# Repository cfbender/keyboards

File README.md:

# The Society of the Crossed Keys

In here you will find my growing list of mechanical keyboard design projects, some of which have been run as local or larger GBs with [KeyHive](https://www.keyhive.xyz).

Please let me know if you have any questions with ordering any PCBs (or let me know if you do it regardless!), or have any questions on how they are designed or function.

Please feel free to open any issues with any cases or PCBs that you have here, and I will do my best to address them!

### Acrylic Case Info

All of my acrylic case files follow the below naming standard:
- All layers are numbered starting with 0, and are numbered up from the bottom
- All layers will be designated with `L<layer number>`
- All feet layers will be designated with `F<layer number>`
- All M3 cases use M3x20mm screws that tap directly into the bottom layer
- All M2 cases will use M3x15+3mm male-to-female brass barrel standoffs where the standoff taps directly into the bottom layer, and M2x6mm screws to screw into the female end of the standoff
- All feet have M4 holes, but I typically have been using M3x14mm screws with M3 nuts on the inside

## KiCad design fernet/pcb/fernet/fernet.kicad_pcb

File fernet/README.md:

# Fernet (_fur-net_)

_"Fernet is an Italian type of amaro, a bitter, aromatic spirit. Fernet is made from a number of herbs and spices which vary according to the brand, but usually include myrrh, rhubarb, chamomile, cardamom, aloe, and especially saffron, with a base of grape distilled spirits."_

A 75% keyboard with a rotary encoder.

This one is really for me since it is only one layout and SMD Elite-C only, but figured I'd put it up here in case anyone is interested in an open source spaced F-row 75% board. More details to follow after initial build.

[Firmware](https://github.com/cfbender/qmk_firmware/tree/fernet/keyboards/fernet)

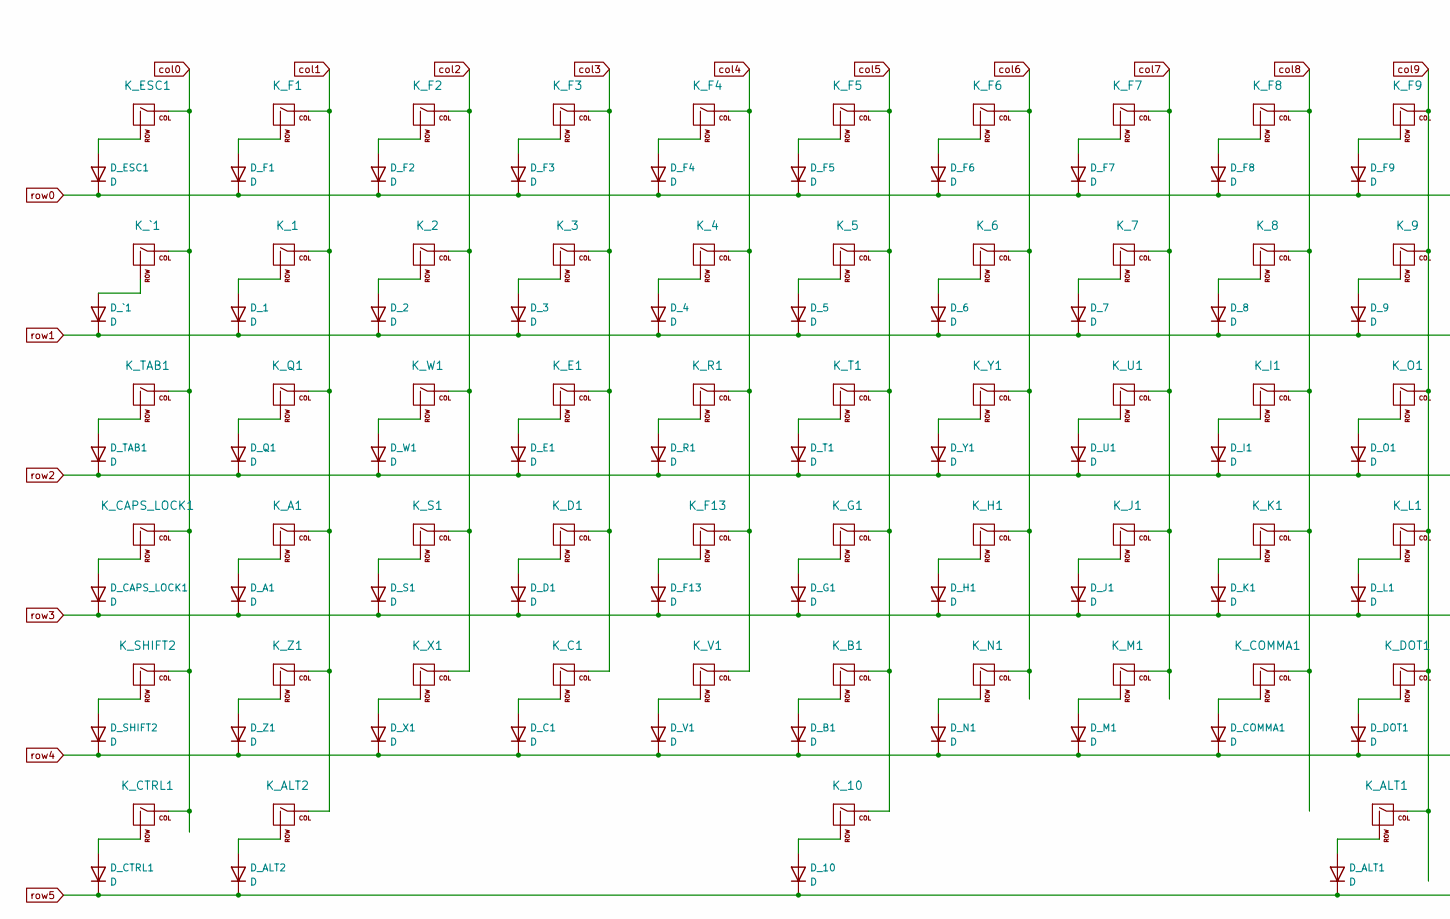
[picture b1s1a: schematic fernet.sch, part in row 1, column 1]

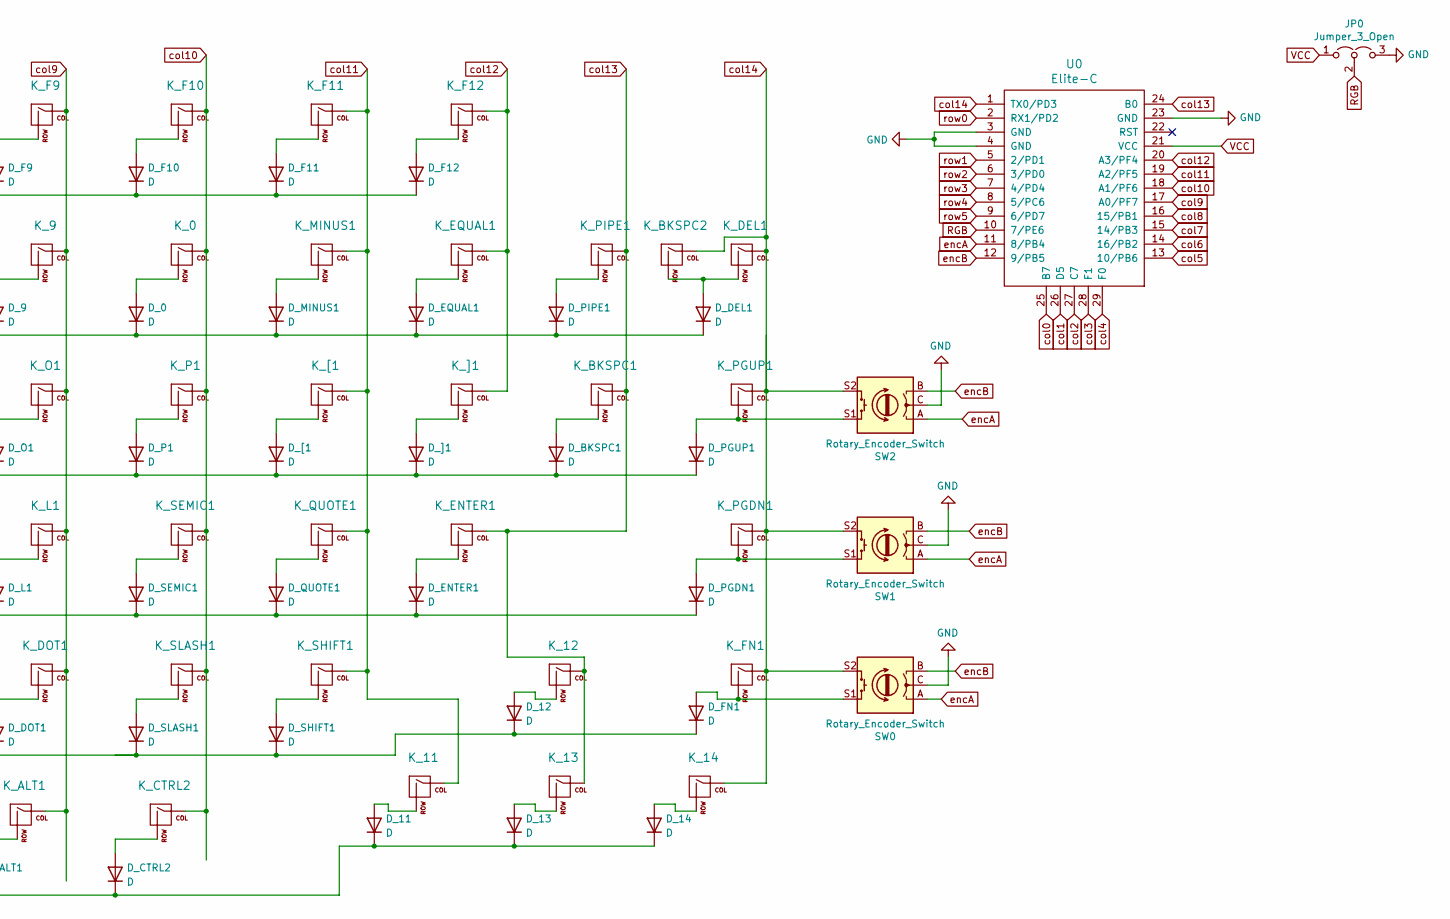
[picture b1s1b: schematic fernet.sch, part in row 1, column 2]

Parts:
D_0, D_1, D_2, D_3, D_4, D_5, D_6, D_7, D_8, D_9, D_10, D_11, D_12, D_13, D_14: D; Diode-Hybrid-Back
D_A1: D; Diode-Hybrid-Back
D_ALT1, D_ALT2: D; Diode-Hybrid-Back
D_B1: D; Diode-Hybrid-Back
D_BKSPC1: D; Diode-Hybrid-Back
D_C1: D; Diode-Hybrid-Back
D_CAPS_LOCK1: D; Diode-Hybrid-Back
D_COMMA1: D; Diode-Hybrid-Back
D_CTRL1, D_CTRL2: D; Diode-Hybrid-Back
D_D1: D; Diode-Hybrid-Back
D_DEL1: D; Diode-Hybrid-Back
D_DOT1: D; Diode-Hybrid-Back
D_E1: D; Diode-Hybrid-Back
D_ENTER1: D; Diode-Hybrid-Back
D_EQUAL1: D; Diode-Hybrid-Back
D_ESC1: D; Diode-Hybrid-Back
D_F1, D_F2, D_F3, D_F4, D_F5, D_F6, D_F7, D_F8, D_F9, D_F10, D_F11, D_F12, D_F13: D; Diode-Hybrid-Back
D_FN1: D; Diode-Hybrid-Back
D_G1: D; Diode-Hybrid-Back
D_H1: D; Diode-Hybrid-Back
D_I1: D; Diode-Hybrid-Back
D_J1: D; Diode-Hybrid-Back
D_K1: D; Diode-Hybrid-Back
D_L1: D; Diode-Hybrid-Back
D_M1: D; Diode-Hybrid-Back
D_MINUS1: D; Diode-Hybrid-Back
D_N1: D; Diode-Hybrid-Back
D_O1: D; Diode-Hybrid-Back
D_P1: D; Diode-Hybrid-Back
D_PGDN1: D; Diode-Hybrid-Back
D_PGUP1: D; Diode-Hybrid-Back
D_PIPE1: D; Diode-Hybrid-Back
D_Q1: D; Diode-Hybrid-Back
D_QUOTE1: D; Diode-Hybrid-Back
D_R1: D; Diode-Hybrid-Back
D_S1: D; Diode-Hybrid-Back
D_SEMIC1: D; Diode-Hybrid-Back
D_SHIFT1, D_SHIFT2: D; Diode-Hybrid-Back
D_SLASH1: D; Diode-Hybrid-Back
D_T1: D; Diode-Hybrid-Back
D_TAB1: D; Diode-Hybrid-Back
D_U1: D; Diode-Hybrid-Back
D_V1: D; Diode-Hybrid-Back
D_W1: D; Diode-Hybrid-Back
D_X1: D; Diode-Hybrid-Back
D_Y1: D; Diode-Hybrid-Back
D_Z1: D; Diode-Hybrid-Back
D_[1: D; Diode-Hybrid-Back
D_]1: D; Diode-Hybrid-Back
D_`1: D; Diode-Hybrid-Back
JP0: Jumper_3_Open; SolderJumperRight
K_0, K_1, K_2, K_3, K_4, K_5, K_6, K_7, K_8, K_9, K_11, K_12, K_13, K_14: KEYSW; MXOnly-1U-NoLED
K_10: KEYSW; MXOnly-7U-ReversedStabilizers-NoLED
K_A1: KEYSW; MXOnly-1U-NoLED
K_ALT1, K_ALT2: KEYSW; MXOnly-1.5U-NoLED
K_B1: KEYSW; MXOnly-1U-NoLED
K_BKSPC1: KEYSW; MXOnly-1.5U-NoLED
K_BKSPC2: KEYSW; MXOnly-2U-NoLED
K_C1: KEYSW; MXOnly-1U-NoLED
K_CAPS_LOCK1: KEYSW; MXOnly-1.75U-NoLED
K_COMMA1: KEYSW; MXOnly-1U-NoLED
K_CTRL1, K_CTRL2: KEYSW; MXOnly-1.5U-NoLED
K_D1: KEYSW; MXOnly-1U-NoLED
K_DEL1: KEYSW; MXOnly-1U-NoLED
K_DOT1: KEYSW; MXOnly-1U-NoLED
K_E1: KEYSW; MXOnly-1U-NoLED
K_ENTER1: KEYSW; MXOnly-2.25U-NoLED
K_EQUAL1: KEYSW; MXOnly-1U-NoLED
K_ESC1: KEYSW; MXOnly-1U-NoLED
K_F1, K_F2, K_F3, K_F4, K_F5, K_F6, K_F7, K_F8, K_F9, K_F10, K_F11, K_F12, K_F13: KEYSW; MXOnly-1U-NoLED
K_FN1: KEYSW; MXOnly-1U-NoLED
K_G1: KEYSW; MXOnly-1U-NoLED
K_H1: KEYSW; MXOnly-1U-NoLED
K_I1: KEYSW; MXOnly-1U-NoLED
K_J1: KEYSW; MXOnly-1U-NoLED
K_K1: KEYSW; MXOnly-1U-NoLED
K_L1: KEYSW; MXOnly-1U-NoLED
K_M1: KEYSW; MXOnly-1U-NoLED
K_MINUS1: KEYSW; MXOnly-1U-NoLED
K_N1: KEYSW; MXOnly-1U-NoLED
K_O1: KEYSW; MXOnly-1U-NoLED
K_P1: KEYSW; MXOnly-1U-NoLED
K_PGDN1: KEYSW; MXOnly-1U-NoLED
K_PGUP1: KEYSW; MXOnly-1U-NoLED
K_PIPE1: KEYSW; MXOnly-1U-NoLED
K_Q1: KEYSW; MXOnly-1U-NoLED
K_QUOTE1: KEYSW; MXOnly-1U-NoLED
K_R1: KEYSW; MXOnly-1U-NoLED
K_S1: KEYSW; MXOnly-1U-NoLED
K_SEMIC1: KEYSW; MXOnly-1U-NoLED
K_SHIFT1: KEYSW; MXOnly-1.75U-NoLED
K_SHIFT2: KEYSW; MXOnly-2.25U-NoLED
K_SLASH1: KEYSW; MXOnly-1U-NoLED
K_T1: KEYSW; MXOnly-1U-NoLED
K_TAB1: KEYSW; MXOnly-1.5U-NoLED
K_U1: KEYSW; MXOnly-1U-NoLED
K_V1: KEYSW; MXOnly-1U-NoLED
K_W1: KEYSW; MXOnly-1U-NoLED
K_X1: KEYSW; MXOnly-1U-NoLED
K_Y1: KEYSW; MXOnly-1U-NoLED
K_Z1: KEYSW; MXOnly-1U-NoLED
K_[1: KEYSW; MXOnly-1U-NoLED
K_]1: KEYSW; MXOnly-1U-NoLED
K_`1: KEYSW; MXOnly-1U-NoLED
SW0, SW1, SW2: Rotary_Encoder_Switch; RotaryEncoder_Alps_EC11E-Switch_Vertical_H20mm
U0: Elite-C; Elite-C-castellated-29pin

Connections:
GND: JP0.3 (B), SW0.C, SW1.C, SW2.C, U0.3 (GND), U0.4 (GND), U0.23 (GND)
unnamed: D_0.2 (A), K_0.2 (ROW)
unnamed: D_1.2 (A), K_1.2 (ROW)
unnamed: D_2.2 (A), K_2.2 (ROW)
unnamed: D_3.2 (A), K_3.2 (ROW)
unnamed: D_4.2 (A), K_4.2 (ROW)
unnamed: D_5.2 (A), K_5.2 (ROW)
unnamed: D_6.2 (A), K_6.2 (ROW)
unnamed: D_7.2 (A), K_7.2 (ROW)
unnamed: D_8.2 (A), K_8.2 (ROW)
unnamed: D_9.2 (A), K_9.2 (ROW)
unnamed: D_10.2 (A), K_10.2 (ROW)
unnamed: D_11.2 (A), K_11.2 (ROW)
unnamed: D_12.2 (A), K_12.2 (ROW)
unnamed: D_13.2 (A), K_13.2 (ROW)
unnamed: D_14.2 (A), K_14.2 (ROW)
unnamed: D_A1.2 (A), K_A1.2 (ROW)
unnamed: D_ALT1.2 (A), K_ALT1.2 (ROW)
unnamed: D_ALT2.2 (A), K_ALT2.2 (ROW)
unnamed: D_B1.2 (A), K_B1.2 (ROW)
unnamed: D_BKSPC1.2 (A), K_BKSPC1.2 (ROW)
unnamed: D_C1.2 (A), K_C1.2 (ROW)
unnamed: D_CAPS_LOCK1.2 (A), K_CAPS_LOCK1.2 (ROW)
unnamed: D_COMMA1.2 (A), K_COMMA1.2 (ROW)
unnamed: D_CTRL1.2 (A), K_CTRL1.2 (ROW)
unnamed: D_CTRL2.2 (A), K_CTRL2.2 (ROW)
unnamed: D_D1.2 (A), K_D1.2 (ROW)
unnamed: D_DEL1.2 (A), K_BKSPC2.2 (ROW), K_DEL1.2 (ROW)
unnamed: D_DOT1.2 (A), K_DOT1.2 (ROW)
unnamed: D_E1.2 (A), K_E1.2 (ROW)
unnamed: D_ENTER1.2 (A), K_ENTER1.2 (ROW)
unnamed: D_EQUAL1.2 (A), K_EQUAL1.2 (ROW)
unnamed: D_ESC1.2 (A), K_ESC1.2 (ROW)
unnamed: D_F1.2 (A), K_F1.2 (ROW)
unnamed: D_F2.2 (A), K_F2.2 (ROW)
unnamed: D_F3.2 (A), K_F3.2 (ROW)
unnamed: D_F4.2 (A), K_F4.2 (ROW)
unnamed: D_F5.2 (A), K_F5.2 (ROW)
unnamed: D_F6.2 (A), K_F6.2 (ROW)
unnamed: D_F7.2 (A), K_F7.2 (ROW)
unnamed: D_F8.2 (A), K_F8.2 (ROW)
unnamed: D_F9.2 (A), K_F9.2 (ROW)
unnamed: D_F10.2 (A), K_F10.2 (ROW)
unnamed: D_F11.2 (A), K_F11.2 (ROW)
unnamed: D_F12.2 (A), K_F12.2 (ROW)
unnamed: D_F13.2 (A), K_F13.2 (ROW)
unnamed: D_FN1.2 (A), K_FN1.2 (ROW), SW0.S1
unnamed: D_G1.2 (A), K_G1.2 (ROW)
unnamed: D_H1.2 (A), K_H1.2 (ROW)
unnamed: D_I1.2 (A), K_I1.2 (ROW)
unnamed: D_J1.2 (A), K_J1.2 (ROW)
unnamed: D_K1.2 (A), K_K1.2 (ROW)
unnamed: D_L1.2 (A), K_L1.2 (ROW)
unnamed: D_M1.2 (A), K_M1.2 (ROW)
unnamed: D_MINUS1.2 (A), K_MINUS1.2 (ROW)
unnamed: D_N1.2 (A), K_N1.2 (ROW)
unnamed: D_O1.2 (A), K_O1.2 (ROW)
unnamed: D_P1.2 (A), K_P1.2 (ROW)
unnamed: D_PGDN1.2 (A), K_PGDN1.2 (ROW), SW1.S1
unnamed: D_PGUP1.2 (A), K_PGUP1.2 (ROW), SW2.S1
unnamed: D_PIPE1.2 (A), K_PIPE1.2 (ROW)
unnamed: D_Q1.2 (A), K_Q1.2 (ROW)
unnamed: D_QUOTE1.2 (A), K_QUOTE1.2 (ROW)
unnamed: D_R1.2 (A), K_R1.2 (ROW)
unnamed: D_S1.2 (A), K_S1.2 (ROW)
unnamed: D_SEMIC1.2 (A), K_SEMIC1.2 (ROW)
unnamed: D_SHIFT1.2 (A), K_SHIFT1.2 (ROW)
unnamed: D_SHIFT2.2 (A), K_SHIFT2.2 (ROW)
unnamed: D_SLASH1.2 (A), K_SLASH1.2 (ROW)
unnamed: D_T1.2 (A), K_T1.2 (ROW)
unnamed: D_TAB1.2 (A), K_TAB1.2 (ROW)
unnamed: D_U1.2 (A), K_U1.2 (ROW)
unnamed: D_V1.2 (A), K_V1.2 (ROW)
unnamed: D_W1.2 (A), K_W1.2 (ROW)
unnamed: D_X1.2 (A), K_X1.2 (ROW)
unnamed: D_Y1.2 (A), K_Y1.2 (ROW)
unnamed: D_Z1.2 (A), K_Z1.2 (ROW)
unnamed: D_[1.2 (A), K_[1.2 (ROW)
unnamed: D_]1.2 (A), K_]1.2 (ROW)
unnamed: D_`1.2 (A), K_`1.2 (ROW)
RGB: JP0.2 (C), U0.10 (7/PE6)
VCC: JP0.1 (A), U0.21 (VCC)
col0: K_CAPS_LOCK1.1 (COL), K_CTRL1.1 (COL), K_ESC1.1 (COL), K_SHIFT2.1 (COL), K_TAB1.1 (COL), K_`1.1 (COL), U0.25 (B7)
col1: K_1.1 (COL), K_A1.1 (COL), K_ALT2.1 (COL), K_F1.1 (COL), K_Q1.1 (COL), K_Z1.1 (COL), U0.26 (D5)
col2: K_2.1 (COL), K_F2.1 (COL), K_S1.1 (COL), K_W1.1 (COL), K_X1.1 (COL), U0.27 (C7)
col3: K_3.1 (COL), K_C1.1 (COL), K_D1.1 (COL), K_E1.1 (COL), K_F3.1 (COL), U0.28 (F1)
col4: K_4.1 (COL), K_F4.1 (COL), K_F13.1 (COL), K_R1.1 (COL), K_V1.1 (COL), U0.29 (F0)
col5: K_5.1 (COL), K_10.1 (COL), K_B1.1 (COL), K_F5.1 (COL), K_G1.1 (COL), K_T1.1 (COL), U0.13 (10/PB6)
col6: K_6.1 (COL), K_F6.1 (COL), K_H1.1 (COL), K_N1.1 (COL), K_Y1.1 (COL), U0.14 (16/PB2)
col7: K_7.1 (COL), K_F7.1 (COL), K_J1.1 (COL), K_M1.1 (COL), K_U1.1 (COL), U0.15 (14/PB3)
col8: K_8.1 (COL), K_COMMA1.1 (COL), K_F8.1 (COL), K_I1.1 (COL), K_K1.1 (COL), U0.16 (15/PB1)
col9: K_9.1 (COL), K_ALT1.1 (COL), K_DOT1.1 (COL), K_F9.1 (COL), K_L1.1 (COL), K_O1.1 (COL), U0.17 (A0/PF7)
col10: K_0.1 (COL), K_CTRL2.1 (COL), K_F10.1 (COL), K_P1.1 (COL), K_SEMIC1.1 (COL), K_SLASH1.1 (COL), U0.18 (A1/PF6)
col11: K_11.1 (COL), K_F11.1 (COL), K_MINUS1.1 (COL), K_QUOTE1.1 (COL), K_SHIFT1.1 (COL), K_[1.1 (COL), U0.19 (A2/PF5)
col12: K_EQUAL1.1 (COL), K_F12.1 (COL), K_]1.1 (COL), U0.20 (A3/PF4)
col13: K_12.1 (COL), K_13.1 (COL), K_BKSPC1.1 (COL), K_ENTER1.1 (COL), K_PIPE1.1 (COL), U0.24 (B0)
col14: K_14.1 (COL), K_BKSPC2.1 (COL), K_DEL1.1 (COL), K_FN1.1 (COL), K_PGDN1.1 (COL), K_PGUP1.1 (COL), SW0.S2, SW1.S2, SW2.S2, U0.1 (TX0/PD3)
encA: SW0.A, SW1.A, SW2.A, U0.11 (8/PB4)
encB: SW0.B, SW1.B, SW2.B, U0.12 (9/PB5)
row0: D_ESC1.1 (K), D_F1.1 (K), D_F2.1 (K), D_F3.1 (K), D_F4.1 (K), D_F5.1 (K), D_F6.1 (K), D_F7.1 (K), D_F8.1 (K), D_F9.1 (K), D_F10.1 (K), D_F11.1 (K), D_F12.1 (K), U0.2 (RX1/PD2)
row1: D_0.1 (K), D_1.1 (K), D_2.1 (K), D_3.1 (K), D_4.1 (K), D_5.1 (K), D_6.1 (K), D_7.1 (K), D_8.1 (K), D_9.1 (K), D_DEL1.1 (K), D_EQUAL1.1 (K), D_MINUS1.1 (K), D_PIPE1.1 (K), D_`1.1 (K), U0.5 (2/PD1)
row2: D_BKSPC1.1 (K), D_E1.1 (K), D_I1.1 (K), D_O1.1 (K), D_P1.1 (K), D_PGUP1.1 (K), D_Q1.1 (K), D_R1.1 (K), D_T1.1 (K), D_TAB1.1 (K), D_U1.1 (K), D_W1.1 (K), D_Y1.1 (K), D_[1.1 (K), D_]1.1 (K), U0.6 (3/PD0)
row3: D_A1.1 (K), D_CAPS_LOCK1.1 (K), D_D1.1 (K), D_ENTER1.1 (K), D_F13.1 (K), D_G1.1 (K), D_H1.1 (K), D_J1.1 (K), D_K1.1 (K), D_L1.1 (K), D_PGDN1.1 (K), D_QUOTE1.1 (K), D_S1.1 (K), D_SEMIC1.1 (K), U0.7 (4/PD4)
row4: D_12.1 (K), D_B1.1 (K), D_C1.1 (K), D_COMMA1.1 (K), D_DOT1.1 (K), D_FN1.1 (K), D_M1.1 (K), D_N1.1 (K), D_SHIFT1.1 (K), D_SHIFT2.1 (K), D_SLASH1.1 (K), D_V1.1 (K), D_X1.1 (K), D_Z1.1 (K), U0.8 (5/PC6)
row5: D_10.1 (K), D_11.1 (K), D_13.1 (K), D_14.1 (K), D_ALT1.1 (K), D_ALT2.1 (K), D_CTRL1.1 (K), D_CTRL2.1 (K), U0.9 (6/PD7)

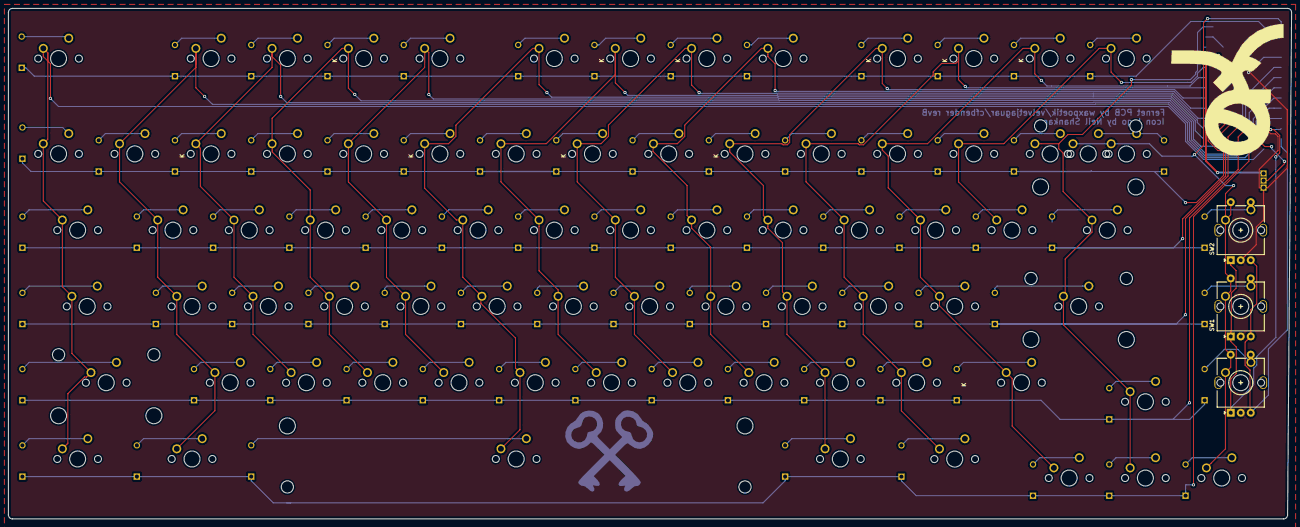
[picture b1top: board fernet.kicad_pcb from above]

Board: 2 copper layers, 320.5 x 127.5 mm, 164 parts (1 on the bottom side), 105 nets.

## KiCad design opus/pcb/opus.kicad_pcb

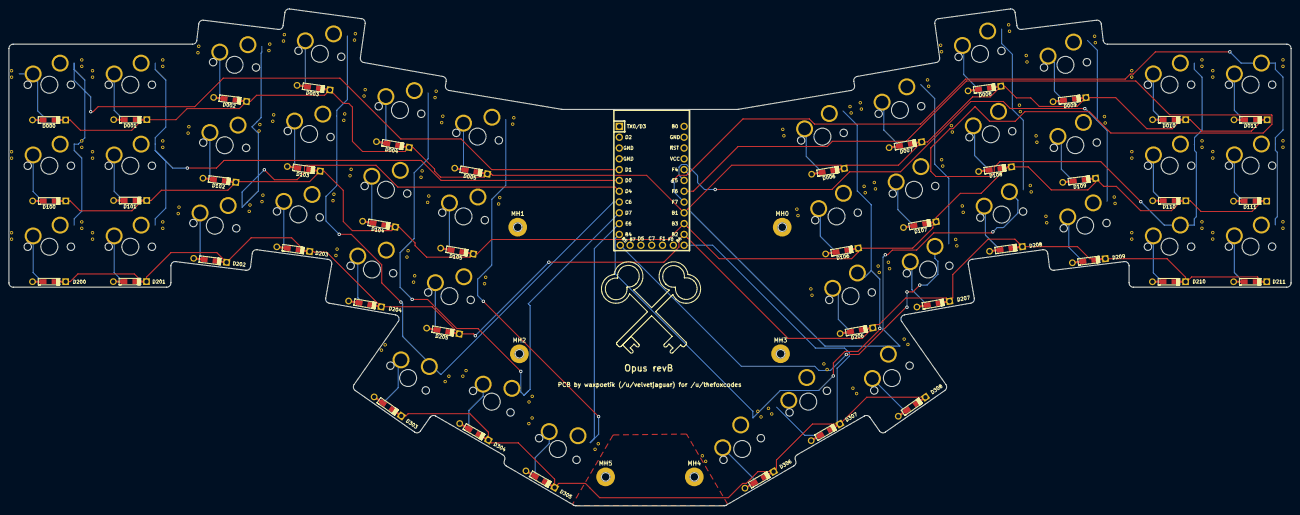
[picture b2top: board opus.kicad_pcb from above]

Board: 2 copper layers, 301.6 x 116.9 mm, 91 parts (0 on the bottom side), 59 nets.

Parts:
D000, D001, D002, D003, D004, D005, D006, D007, D008, D009, D010, D011, D100, D101, D102, D103, D104, D105, D106, D107, D108, D109, D110, D111, D200, D201, D202, D203, D204, D205, D206, D207, D208, D209, D210, D211, D303, D304, D305, D306, D307, D308: 1N4148; Diode-dual
K000, K001, K002, K003, K004, K005, K006, K007, K008, K009, K010, K011, K100, K101, K102, K103, K104, K105, K106, K107, K108, K109, K110, K111, K200, K201, K202, K203, K204, K205, K206, K207, K208, K209, K210, K211, K303, K304, K305, K306, K307, K308: KEYSW; MXOnly-1U-Hotswap-Antishear
MH0, MH1, MH2, MH3, MH4, MH5: MountingHole_Pad; MountingHole_2.2mm_M2_Pad
U0: ProMicro; Elite-C

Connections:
GND: U0.3, U0.4, U0.23
unnamed: D000.2, K000.1
unnamed: D001.2, K001.1
unnamed: D002.2, K002.1
unnamed: D003.2, K003.1
unnamed: D004.2, K004.1
unnamed: D005.2, K005.1
unnamed: D006.2, K006.1
unnamed: D007.2, K007.1
unnamed: D008.2, K008.1
unnamed: D009.2, K009.1
unnamed: D010.2, K010.1
unnamed: D011.2, K011.1
unnamed: D100.2, K100.1
unnamed: D101.2, K101.1
unnamed: D102.2, K102.1
unnamed: D103.2, K103.1
unnamed: D104.2, K104.1
unnamed: D105.2, K105.1
unnamed: D106.2, K106.1
unnamed: D107.2, K107.1
unnamed: D108.2, K108.1
unnamed: D109.2, K109.1
unnamed: D110.2, K110.1
unnamed: D111.2, K111.1
unnamed: D200.2, K200.1
unnamed: D201.2, K201.1
unnamed: D202.2, K202.1
unnamed: D203.2, K203.1
unnamed: D204.2, K204.1
unnamed: D205.2, K205.1
unnamed: D206.2, K206.1
unnamed: D207.2, K207.1
unnamed: D208.2, K208.1
unnamed: D209.2, K209.1
unnamed: D210.2, K210.1
unnamed: D211.2, K211.1
unnamed: D303.2, K303.1
unnamed: D304.2, K304.1
unnamed: D305.2, K305.1
unnamed: D306.2, K306.1
unnamed: D307.2, K307.1
unnamed: D308.2, K308.1
col0: K000.2, K100.2, K200.2, U0.5
col1: K001.2, K101.2, K201.2, U0.6
col2: K002.2, K102.2, K202.2, U0.7
col3: K003.2, K103.2, K203.2, K303.2, U0.8
col4: K004.2, K104.2, K204.2, K304.2, U0.9
col5: K005.2, K105.2, K205.2, K305.2, U0.10
col6: K006.2, K106.2, K206.2, K306.2, U0.11
col7: K007.2, K107.2, K207.2, K307.2, U0.12
col8: K008.2, K108.2, K208.2, K308.2, U0.20
col9: K009.2, K109.2, K209.2, U0.19
col10: K010.2, K110.2, K210.2, U0.18
col11: K011.2, K111.2, K211.2, U0.17
row0: D000.1, D001.1, D002.1, D003.1, D004.1, D005.1, D006.1, D007.1, D008.1, D009.1, D010.1, D011.1, U0.16
row1: D100.1, D101.1, D102.1, D103.1, D104.1, D105.1, D106.1, D107.1, D108.1, D109.1, D110.1, D111.1, U0.15
row2: D200.1, D201.1, D202.1, D203.1, D204.1, D205.1, D206.1, D207.1, D208.1, D209.1, D210.1, D211.1, U0.14
row3: D303.1, D304.1, D305.1, D306.1, D307.1, D308.1, U0.13

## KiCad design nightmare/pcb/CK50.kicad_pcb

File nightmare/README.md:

# Crossed Keys Nightmare

A 50% pseudo-TMO50 clone with an adjusted bottom row, designed on the cheap with a Pro Micro and 3D Printed case.

Keyboard/Case Designer: [cfbender](https://github.com/codybender) with help from Reggatronics/Reggalicious

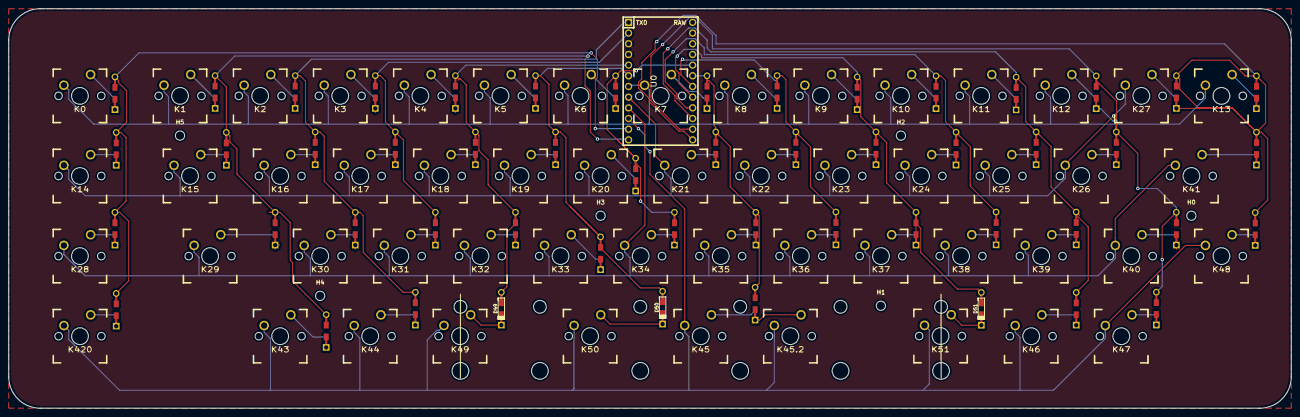
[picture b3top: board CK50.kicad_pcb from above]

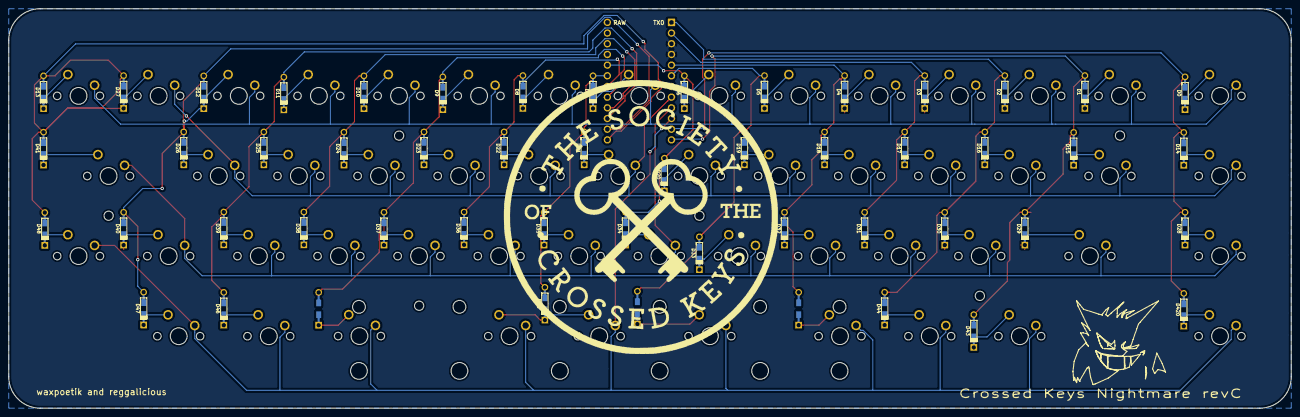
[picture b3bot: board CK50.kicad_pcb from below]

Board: 2 copper layers, 305.0 x 95.0 mm, 112 parts (49 on the bottom side), 70 nets.

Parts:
D0, D1, D2, D3, D4, D5, D6, D7, D8, D9, D10, D11, D12, D13, D14, D15, D16, D17, D18, D19, D20, D21, D22, D23, D24, D25, D26, D27, D28, D29, D30, D31, D32, D33, D34, D35, D36, D37, D38, D39, D40, D41, D43, D44, D45, D46, D47, D48, D49, D50, D51, D420: 1N4148; Diode-dual
H0, H1, H2, H3, H4, H5: MountingHole_2.2mm_M2
K0, K1, K2, K3, K4, K5, K6, K7, K8, K9, K10, K11, K12, K13, K14, K16, K17, K18, K19, K20, K21, K22, K23, K24, K25, K26, K27, K28, K30, K31, K32, K33, K34, K35, K36, K37, K38, K39, K43, K47, K48, K49, K51, K420: KEYSW; MX_PCB_100H
K15, K40, K44, K46: KEYSW; MX_PCB_125H
K29, K41: KEYSW; MX_PCB_175H
K45: KEYSW; MX_PCB_700H
K45.2: KEYSW; MX_PCB_275H
K50: KEYSW; MX_PCB_225H
U0: ProMicro; ARDUINO_PRO_MICRO

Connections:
/col0: D0.2, D14.2, D28.2, D420.2, U0.11
/col1: D1.2, D15.2, D29.2, D43.2, U0.12
/col2: D2.2, D16.2, D30.2, D44.2, U0.1
/col3: D3.2, D17.2, D31.2, U0.2
/col4: D4.2, D18.2, D32.2, D49.2, U0.5
/col5: D5.2, D19.2, D33.2, D50.2, U0.6
/col6: D6.2, D20.2, D34.2, U0.20
/col7: D7.2, D21.2, D35.2, D45.2, U0.19
/col8: D8.2, D22.2, D36.2, U0.18
/col9: D9.2, D23.2, D37.2, D51.2, U0.17
/col10: D10.1, D10.2, D24.2, D38.2, K10.1, U0.16
/col11: D11.2, D25.2, D39.2, D46.2, U0.15
/col12: D12.2, D26.2, D40.2, D47.2, U0.14
/col13: D13.2, D27.2, D41.2, D48.2, U0.13
/row0: K0.2, K1.2, K2.2, K3.2, K4.2, K5.2, K6.2, K7.2, K8.2, K9.2, K10.2, K11.2, K12.2, K13.2, U0.7
/row1: K14.2, K15.2, K16.2, K17.2, K18.2, K19.2, K20.2, K21.2, K22.2, K23.2, K24.2, K25.2, K26.2, K27.2, U0.8
/row2: K28.2, K29.2, K30.2, K31.2, K32.2, K33.2, K34.2, K35.2, K36.2, K37.2, K38.2, K39.2, K40.2, K41.2, U0.9
/row3: K43.2, K44.2, K45.2, K45.2.2, K46.2, K47.2, K48.2, K49.2, K50.2, K51.2, K420.2, U0.10
GND: U0.3, U0.4, U0.23
unnamed: D0.1, K0.1
unnamed: D1.1, K1.1
unnamed: D2.1, K2.1
unnamed: D3.1, K3.1
unnamed: D4.1, K4.1
unnamed: D5.1, K5.1
unnamed: D6.1, K6.1
unnamed: D7.1, K7.1
unnamed: D8.1, K8.1
unnamed: D9.1, K9.1
unnamed: D11.1, K11.1
unnamed: D12.1, K12.1
unnamed: D13.1, K13.1
unnamed: D14.1, K14.1
unnamed: D15.1, K15.1
unnamed: D16.1, K16.1
unnamed: D17.1, K17.1
unnamed: D18.1, K18.1
unnamed: D19.1, K19.1
unnamed: D20.1, K20.1
unnamed: D21.1, K21.1
unnamed: D22.1, K22.1
unnamed: D23.1, K23.1
unnamed: D24.1, K24.1
unnamed: D25.1, K25.1
unnamed: D26.1, K26.1
unnamed: D27.1, K27.1
unnamed: D28.1, K28.1
unnamed: D29.1, K29.1
unnamed: D30.1, K30.1
unnamed: D31.1, K31.1
unnamed: D32.1, K32.1
unnamed: D33.1, K33.1
unnamed: D34.1, K34.1
unnamed: D35.1, K35.1
unnamed: D36.1, K36.1
unnamed: D37.1, K37.1
unnamed: D38.1, K38.1
unnamed: D39.1, K39.1
unnamed: D40.1, K40.1
unnamed: D41.1, K41.1
unnamed: D43.1, K43.1
unnamed: D44.1, K44.1
unnamed: D45.1, K45.1, K45.2.1
unnamed: D46.1, K46.1
unnamed: D47.1, K47.1
unnamed: D48.1, K48.1
unnamed: D49.1, K49.1
unnamed: D50.1, K50.1
unnamed: D51.1, K51.1
unnamed: D420.1, K420.1

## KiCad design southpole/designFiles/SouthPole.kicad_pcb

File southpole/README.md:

# Crossed Keys Southpole

A southpaw numpad with a classic 7u 65% design base.

Keyboard/Case Designer: [Cody Bender](https://github.com/codybender)  

Assembly guide: [On Google Drive](https://drive.google.com/open?id=1JN_OK8rfhoJso8HBKvpQtmv_5men5zyt0q0xczGZrWI)

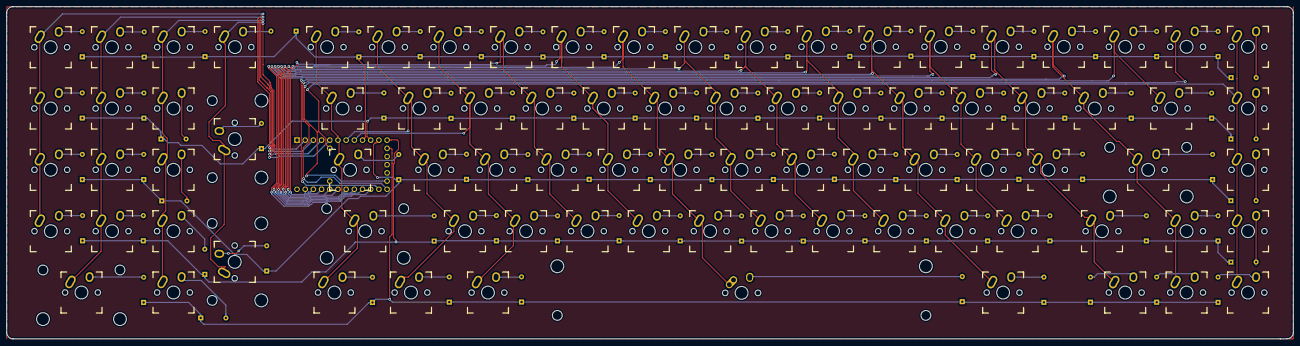
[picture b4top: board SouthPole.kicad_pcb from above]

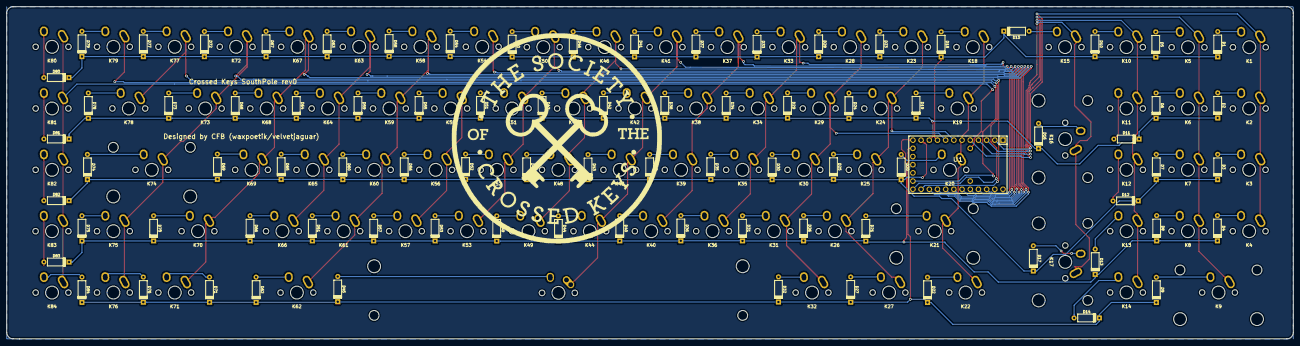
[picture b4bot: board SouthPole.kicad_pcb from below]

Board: 2 copper layers, 399.0 x 103.0 mm, 169 parts (85 on the bottom side), 110 nets.

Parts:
D1, D2, D3, D4, D5, D6, D7, D8, D9, D10, D11, D12, D13, D14, D15, D16, D17, D18, D19, D20, D21, D22, D23, D24, D25, D26, D27, D28, D29, D30, D31, D32, D33, D34, D35, D36, D37, D38, D39, D40, D41, D42, D43, D44, D45, D46, D47, D48, D49, D50, D51, D52, D53, D54, D55, D56, D57, D58, D59, D60, D61, D62, D63, D64, D65, D66, D67, D68, D69, D70, D71, D72, D73, D74, D75, D76, D77, D78, D79, D80, D81, D82, D83, D84: D; D_axial
K1, K2, K3, K4, K5, K6, K7, K8, K10, K11, K12, K13, K14, K15, K18, K23, K24, K25, K26, K28, K29, K30, K31, K33, K34, K35, K36, K37, K38, K39, K40, K41, K42, K43, K44, K46, K47, K48, K49, K50, K51, K52, K53, K54, K55, K56, K57, K58, K59, K60, K61, K63, K64, K65, K66, K67, K68, K69, K71, K72, K73, K75, K76, K77, K79, K80, K81, K82, K83, K84: KEYSW; Mx_Alps_100
K9, K16, K17: KEYSW; Mx_Alps_200
K19, K62, K78: KEYSW; Mx_Alps_150
K20, K70: KEYSW; Mx_Alps_175
K21, K74: KEYSW; Mx_Alps_225
K22, K27, K32: KEYSW; Mx_Alps_125
K45: KEYSW; MX-7U-ReversedStabilizers-NoLED
U1: TEENSY2.0; Teensy_20

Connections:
/col0: K1.1, K2.1, K3.1, K4.1, U1.2
/col1: K5.1, K6.1, K7.1, K8.1, K9.1, U1.3
/col2: K10.1, K11.1, K12.1, K13.1, K14.1, U1.4
/col3: K15.1, K16.1, K17.1, U1.5
/col4: K18.1, K19.1, K20.1, K21.1, K22.1, U1.6
/col5: K23.1, K24.1, K25.1, K26.1, K27.1, U1.7
/col6: K28.1, K29.1, K30.1, K31.1, K32.1, U1.8
/col7: K33.1, K34.1, K35.1, K36.1, U1.28
/col8: K37.1, K38.1, K39.1, K40.1, U1.27
/col9: K41.1, K42.1, K43.1, K44.1, K45.1, U1.26
/col10: K46.1, K47.1, K48.1, K49.1, U1.25
/col11: K50.1, K51.1, K52.1, K53.1, U1.24
/col12: K54.1, K55.1, K56.1, K57.1, U1.23
/col13: K58.1, K59.1, K60.1, K61.1, K62.1, U1.22
/col14: K63.1, K64.1, K65.1, K66.1, U1.21
/col15: K67.1, K68.1, K69.1, K70.1, K71.1, U1.20
/col16: K72.1, K73.1, K74.1, K75.1, K76.1, U1.19
/col17: K77.1, K78.1, U1.18
/col18: K79.1, U1.17
/col19: K80.1, K81.1, K82.1, K83.1, K84.1, U1.31
/row0: D1.1, D5.1, D10.1, D15.1, D18.1, D23.1, D28.1, D33.1, D37.1, D41.1, D46.1, D50.1, D54.1, D58.1, D63.1, D67.1, D72.1, D77.1, D79.1, D80.1, U1.9
/row1: D2.1, D6.1, D11.1, D16.1, D19.1, D24.1, D29.1, D34.1, D38.1, D42.1, D47.1, D51.1, D55.1, D59.1, D64.1, D68.1, D73.1, D78.1, D81.1, U1.10
/row2: D3.1, D7.1, D12.1, D17.1, D20.1, D25.1, D30.1, D35.1, D39.1, D43.1, D48.1, D52.1, D56.1, D60.1, D65.1, D69.1, D74.1, D82.1, U1.11
/row3: D4.1, D8.1, D13.1, D21.1, D26.1, D31.1, D36.1, D40.1, D44.1, D49.1, D53.1, D57.1, D61.1, D66.1, D70.1, D75.1, D83.1, U1.12
/row4: D9.1, D14.1, D22.1, D27.1, D32.1, D45.1, D62.1, D71.1, D76.1, D84.1, U1.13
GND: U1.1, U1.15
unnamed: D1.2, K1.2
unnamed: D2.2, K2.2
unnamed: D3.2, K3.2
unnamed: D4.2, K4.2
unnamed: D5.2, K5.2
unnamed: D6.2, K6.2
unnamed: D7.2, K7.2
unnamed: D8.2, K8.2
unnamed: D9.2, K9.2
unnamed: D10.2, K10.2
unnamed: D11.2, K11.2
unnamed: D12.2, K12.2
unnamed: D13.2, K13.2
unnamed: D14.2, K14.2
unnamed: D15.2, K15.2
unnamed: D16.2, K16.2
unnamed: D17.2, K17.2
unnamed: D18.2, K18.2
unnamed: D19.2, K19.2
unnamed: D20.2, K20.2
unnamed: D21.2, K21.2
unnamed: D22.2, K22.2
unnamed: D23.2, K23.2
unnamed: D24.2, K24.2
unnamed: D25.2, K25.2
unnamed: D26.2, K26.2
unnamed: D27.2, K27.2
unnamed: D28.2, K28.2
unnamed: D29.2, K29.2
unnamed: D30.2, K30.2
unnamed: D31.2, K31.2
unnamed: D32.2, K32.2
unnamed: D33.2, K33.2
unnamed: D34.2, K34.2
unnamed: D35.2, K35.2
unnamed: D36.2, K36.2
unnamed: D37.2, K37.2
unnamed: D38.2, K38.2
unnamed: D39.2, K39.2
unnamed: D40.2, K40.2
unnamed: D41.2, K41.2
unnamed: D42.2, K42.2
unnamed: D43.2, K43.2
unnamed: D44.2, K44.2
unnamed: D45.2, K45.2
unnamed: D46.2, K46.2
unnamed: D47.2, K47.2
unnamed: D48.2, K48.2
unnamed: D49.2, K49.2
unnamed: D50.2, K50.2
unnamed: D51.2, K51.2
unnamed: D52.2, K52.2
unnamed: D53.2, K53.2
unnamed: D54.2, K54.2
unnamed: D55.2, K55.2
unnamed: D56.2, K56.2
unnamed: D57.2, K57.2
unnamed: D58.2, K58.2
unnamed: D59.2, K59.2
unnamed: D60.2, K60.2
unnamed: D61.2, K61.2
unnamed: D62.2, K62.2
unnamed: D63.2, K63.2
unnamed: D64.2, K64.2
unnamed: D65.2, K65.2
unnamed: D66.2, K66.2
unnamed: D67.2, K67.2
unnamed: D68.2, K68.2
unnamed: D69.2, K69.2
unnamed: D70.2, K70.2
unnamed: D71.2, K71.2
unnamed: D72.2, K72.2
unnamed: D73.2, K73.2
unnamed: D74.2, K74.2
unnamed: D75.2, K75.2
unnamed: D76.2, K76.2
unnamed: D77.2, K77.2
unnamed: D78.2, K78.2
unnamed: D79.2, K79.2
unnamed: D80.2, K80.2
unnamed: D81.2, K81.2
unnamed: D82.2, K82.2
unnamed: D83.2, K83.2
unnamed: D84.2, K84.2

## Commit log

2019-07-19 initialized local files
2019-07-20 updated README to link
2019-07-22 updated Nightmare gerber files and added B.mask
2019-08-23 updated PCB for split space
2019-08-23 added qmk source. NEEDS TESTING
2019-08-23 updated PCB for revC and added split space plate
2019-08-26 updated keyhive link in readme
2019-08-26 updated case with split space
2019-08-26 fixed layout for nightmare
2019-08-26 compiled new default layout
2019-08-26 fixed missing wire
2019-08-26 updated readme and render
2019-09-11 Update Nightmare picture
2019-09-11 Add DEL to keymap
2019-09-11 Update from qmk fork
2019-09-11 Update compiled firmare
2019-09-11 Update Keymap from qmk
2019-12-10 Add M4 feet file
2019-12-10 Update M4 feet file
2020-01-14 Update Nightmare top for better stab clearance
2020-01-18 Add initial opus files
2020-01-18 rename PCB directory
2020-01-19 Add Opus revA files
2020-01-22 Add Lattice60 files
2020-01-22 Update Lattice blocker tolerance
2020-01-24 Add acrylic Nightmare
2020-01-27 Update Nightmare PCB to fix NKRO
2020-01-27 Add new Nightmare photo and update README
2020-01-28 Update screw spacing on acrylic Nightmare
2020-01-29 Add case feet
2020-02-01 Add Opus revB with col6 fix
2020-02-12 Add acrylic Launchpad case
2020-03-04 Add full nightmare file
2020-03-09 Add initial Absinthe files
2020-03-09 Add README and SVGs
2020-03-10 Add 2.75u RSFT support to Absinthe
2020-03-10 Update spacebar tolerance on DXFs for Absinthe
2020-03-10 Update Absinthe SVGs
2020-03-13 Remove Absinthe PCB temporarily due to wire error
2020-03-14 Add Absinthe Ponoko files
2020-03-15 Add Absinthe ponoko full plate option
2020-03-15 Remove Absinthe ponoko SVGs
2020-03-15 Update ponoko files and add README for absinthe
2020-03-15 Add width for Ponoko for absinthe
2020-03-15 Rename Absinthe ponoko files
2020-03-19 Update Absinthe top layer tolerances
2020-03-27 Add M4 feet openSCAD file
2020-03-27 Remove old feet file
2020-03-27 Add more absinthe documentation
2020-04-02 Add foam spacing layer for absinthe
2020-05-21 Add Andy case files
2020-05-21 Add M2 L6 for Andy
2020-05-29 Add Fernet PCB and Voyager104 case
2020-05-29 Cleanup fernet files
2020-05-30 Add Fernet gerber and plate
2020-05-30 Add fernet acrylic case
2020-05-30 Add fernet screenshot
2020-05-30 Update fernet readme
2020-05-30 Add gitignore
2020-05-30 Remove ignored files
2020-05-30 Update fernet PCB to fix exposed trace
2020-06-05 Update absinthe bottom for USB clearance
2020-06-05 Add 2u backspace support to fernet
2020-06-05 Add layout picture and update gerber
2020-06-05 Update fernet files
2020-06-05 Update repo readme
2020-06-06 Update fernet files from first prototype
2020-06-07 Fix fernet case files for bottom row
2020-06-14 Add VIA json for fernet
2020-06-29 Add artisan case
2020-07-01 Added VIA support to nightmare
    .json for VIA is in the via folder for the firmware
2020-07-03 Add m-65 foam and color egdes for cut order
2020-07-07 Moved file and changed vendorID as well as productID
2020-07-07 Updated nightmare.json
2020-07-07 Removed changes other than the VIA json file on the keyboard root directory
2020-07-07 removed json from the nightmare qmk firmware folder
2020-07-07 Nightmare VIA support (#2)
    * Added VIA support to nightmare
    .json for VIA is in the via folder for the firmware
    * Update readme.md
    * Moved file and changed vendorID as well as productID
    * Updated nightmare.json
    * Removed changes other than the VIA json file on the keyboard root directory
2020-07-07 Update to MPL2
2020-07-11 Add opus case files
2020-07-11 Remove opus switch plate used for PCB design
2020-07-17 Add printable film and initial quefrency case files
2020-07-17 Update quefrency readme
2020-07-17 Fix missing fernet logo
2020-07-17 Remove uncompressed gerbers
2020-07-19 Add first pass at absinthe VIA json
2020-07-20 Fix absinthe JSON
2020-07-21 Add Lattice M2 files
2020-07-21 Update quefrency case for BEZELS
2020-07-24 Fix quefrency left half feet
2020-07-25 Add corne case files
2020-07-25 Remove nightmare firmware files
2020-07-25 Move m65 foam to misc
2020-08-02 Add 65 right half, fix split bs, longer feet
2020-08-06 Update quefrency cases for stab clearance
2020-08-07 Fix right shift for quefrency
2020-08-08 Fix voyager case edge
2020-08-08 Add voyager stencil
2020-08-08 Add outline to stencil
2020-08-11 Standardize 2u stab cutouts for clearance
2020-10-04 chore: add initial shoebill files
2020-10-08 chore: add keycap tolerance on lattice top files
2020-10-20 feat: add lattice60 3d print case
2020-10-23 feat: shoebill feet and encoder fix
2020-11-13 fix: quefrency stab cutouts for backspace
2020-11-13 feat: change top layers on bdn9 case
2020-11-13 feat: bdn9 acrylic case
2020-11-13 Add BDN9 Acrylic case (#6)
    * feat: bdn9 acrylic case
    * feat: change top layers on bdn9 case
2020-11-13 fix: quefrency stab cutouts for backspace (#9)
2021-03-11 fix: add missing screw holes in right side 65% quefrency L0
2021-03-11 feat: add long quefrency feet
2021-03-30 added wkl .dxf files
2021-03-31 feat: add absinthe blocker svgs, M3 version and filled plate
2021-04-04 feat: add quefrency left macro case
2021-04-30 Create lattice.json
    for use in via
